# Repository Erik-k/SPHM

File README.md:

# SPHM
Solar Powered Home Monitor

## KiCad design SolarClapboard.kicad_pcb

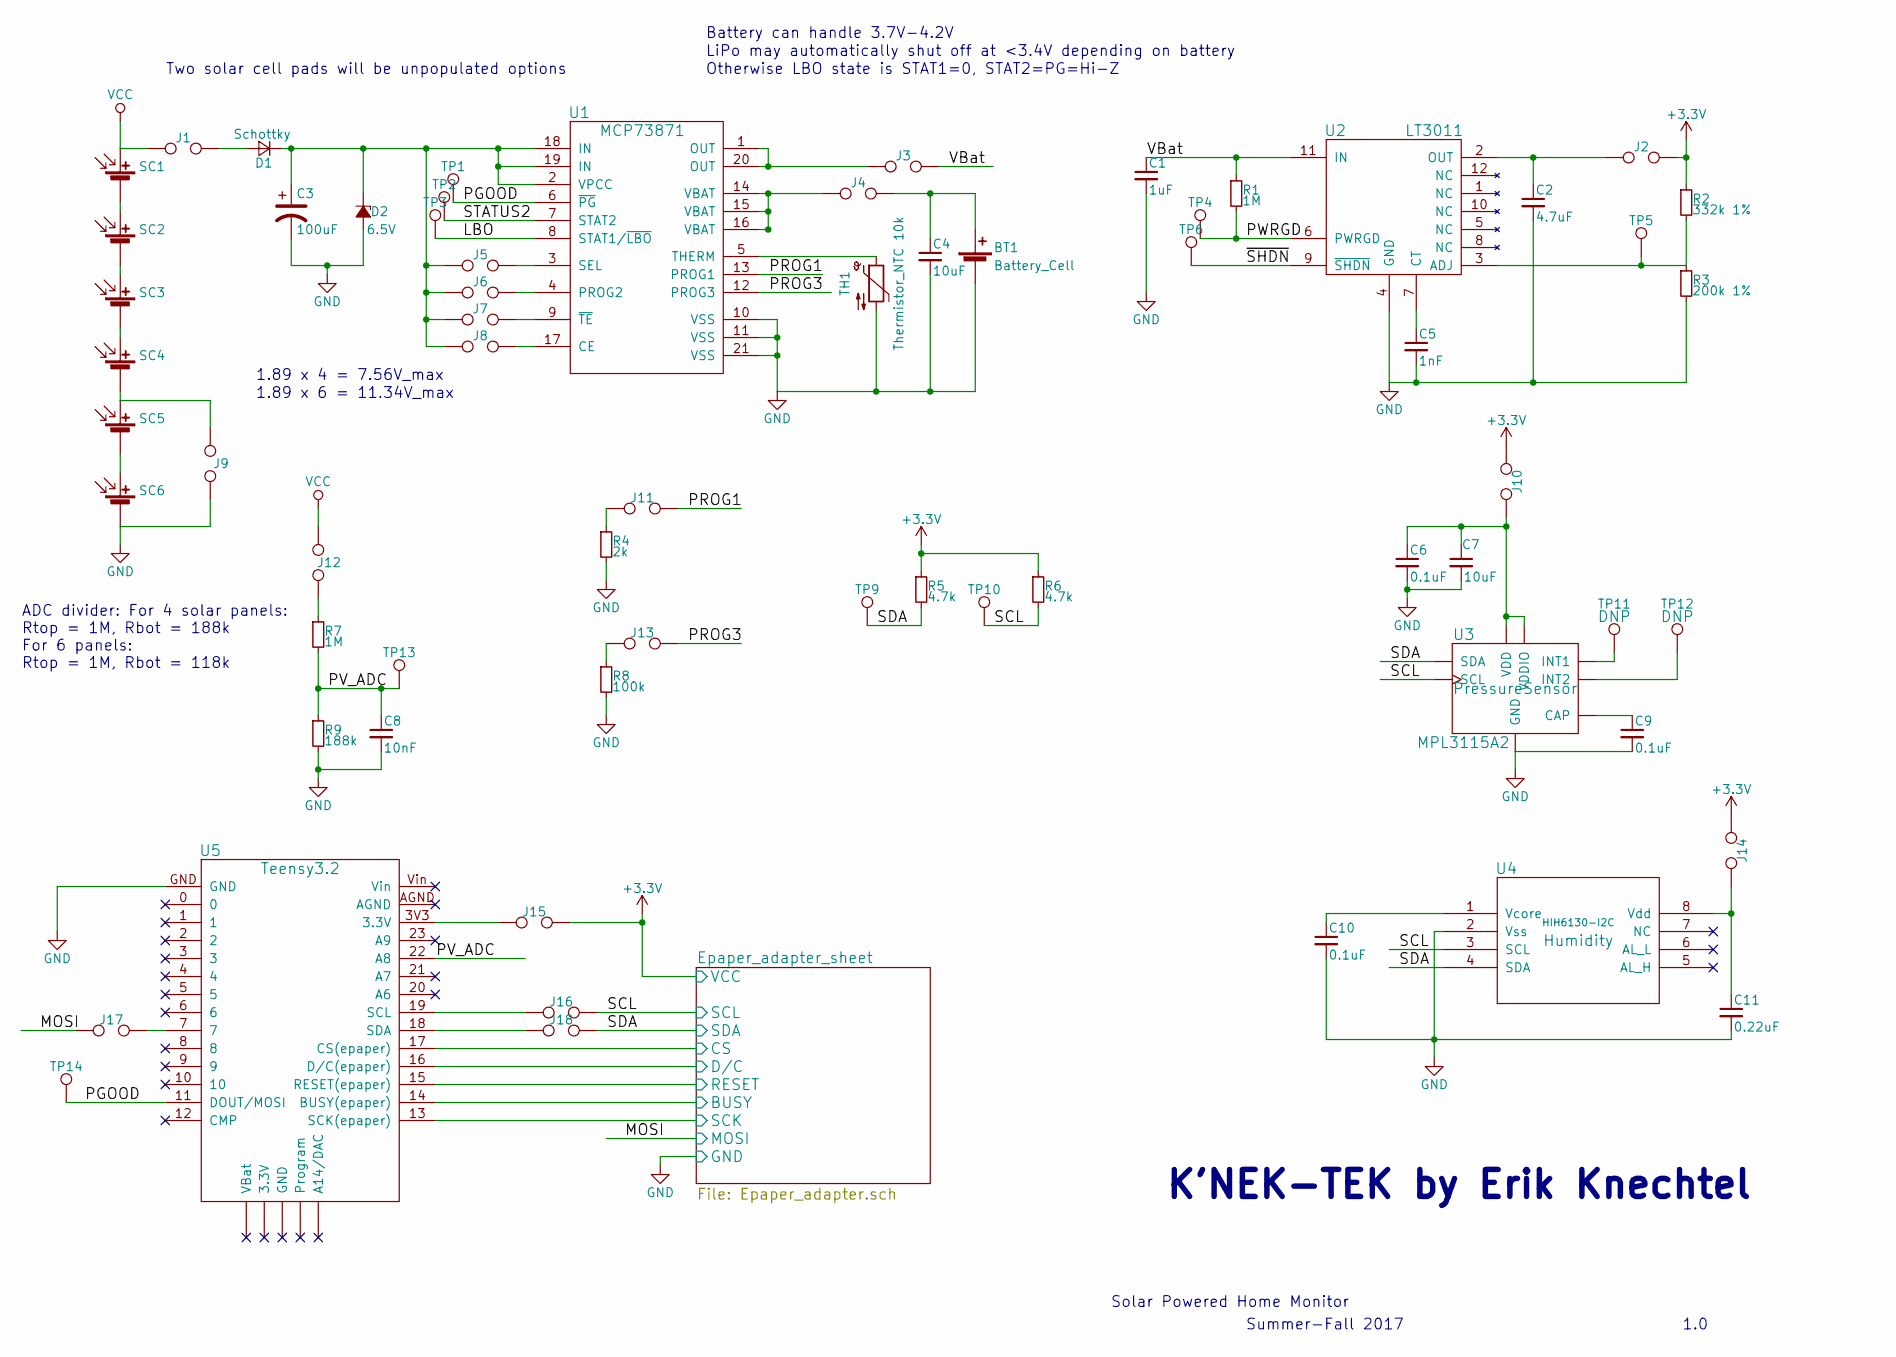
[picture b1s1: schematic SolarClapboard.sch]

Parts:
BT1: Battery_Cell; JST_PH_S2B-PH-SM4-TB_02x2.00mm_Angled
C1: 1uF; C_1206_HandSoldering
C2: 4.7uF; C_1206_HandSoldering
C3: 100uF; CP_Radial_D5.0mm_P2.00mm
C4, C7: 10uF; CP_Radial_D5.0mm_P2.00mm
C5: 1nF; C_1206_HandSoldering
C6, C9, C10: 0.1uF; C_1206_HandSoldering
C8: 10nF; C_1206_HandSoldering
C11: 0.22uF; C_1206_HandSoldering
D1: Schottky; D_SOD-323_HandSoldering; MFG_PN CUS08F30,H3F
D2: 6.5V; D_SOD-323_HandSoldering; MFG_PN DDZ6V8ASF-7
J1, J2, J3, J4, J5, J6, J7, J8, J9, J10, J11, J12, J13, J14, J15, J16, J17, J18: TEST_2P; Test_Point_2Pads
R1, R7: 1M; R_1206_HandSoldering
R2: 332k 1%; R_1206_HandSoldering
R3: 200k 1%; R_1206_HandSoldering
R4: 2k; R_1206_HandSoldering
R5, R6: 4.7k; R_1206_HandSoldering
R8: 100k; R_1206_HandSoldering
R9: 188k; R_1206_HandSoldering
SC1, SC2, SC3, SC4, SC5, SC6: Solar_Cell; MONO_SOLAR_CELL_22MMx7MM_KXOB22-04X3F; MFG_PN KXOB22-04X3F
TH1: Thermistor_NTC 10k; R_Axial_DIN0204_L3.6mm_D1.6mm_P2.54mm_Vertical
TP1, TP2, TP3, TP4, TP5, TP6, TP9, TP10, TP11, TP12, TP13, TP14: TEST_1P; TestPointHole
U1: MCP73871; QFN-20-1EP_4x4mm_Pitch0.5mm
U2: LT3011; MSOP-12_3x4mm_Pitch0.65mm
U3: MPL3115A2; LGA-8_3x5mm_Pitch1.25mm_handsolder
U4: HIH6130-I2C; SO-8_5.3x6.2mm_Pitch1.27mm
U5: Teensy3.2; Teensy_Header_Straight_2x14_Pitch2.54mm

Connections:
+3V3: J2.2, J10.1, J14.1, J15.2, R2.1, R5.1, R6.1; also elsewhere on the board
/Epaper_adapter_sheet/BUSY: U5.14 (BUSY(epaper)); also elsewhere on the board
/Epaper_adapter_sheet/CS: U5.17 (CS(epaper)); also elsewhere on the board
/Epaper_adapter_sheet/D/C: U5.16 (D/C(epaper)); also elsewhere on the board
/Epaper_adapter_sheet/RESET: U5.15 (RESET(epaper)); also elsewhere on the board
/Epaper_adapter_sheet/SCK: U5.13 (SCK(epaper)); also elsewhere on the board
/LBO: TP3.1, U1.8 (STAT1/~LBO)
/MOSI: J17.1; also elsewhere on the board
/PGOOD: TP1.1, TP14.1, U1.6 (~PG), U5.11 (DOUT/MOSI)
/PROG1: J11.2, U1.13 (PROG1)
/PROG3: J13.2, U1.12 (PROG3)
/PV_ADC: C8.1, R7.2, R9.1, TP13.1, U5.22 (A8)
/PWRGD: R1.2, TP4.1, U2.6 (PWRGD)
/SCL: J16.2, R6.2, TP10.1, U3.8 (SCL), U4.3 (SCL)
/SDA: J18.2, R5.2, TP9.1, U3.7 (SDA), U4.4 (SDA)
/STATUS2: TP2.1, U1.7 (STAT2)
/VBat: C1.1, J3.2, R1.1, U2.11 (IN)
/~SHDN: TP6.1, U2.9 (~SHDN)
unnamed: BT1.1 (+), C4.1, J4.2
unnamed: C2.1, J2.1, U2.2 (OUT)
unnamed: C3.1, D1.1 (K), D2.1 (K), J5.1, J6.1, J7.1, J8.1, U1.2 (VPCC), U1.18 (IN), U1.19 (IN)
unnamed: C5.1, U2.7 (CT)
unnamed: C6.1, C7.1, J10.2, U3.1 (VDD), U3.4 (VDDIO)
unnamed: C9.1, U3.2 (CAP)
unnamed: C10.1, U4.1 (Vcore)
unnamed: C11.1, J14.2, U4.8 (Vdd)
unnamed: D1.2 (A), J1.2
unnamed: J3.1, U1.1 (OUT), U1.20 (OUT)
unnamed: J4.1, U1.14 (VBAT), U1.15 (VBAT), U1.16 (VBAT)
unnamed: J5.2, U1.3 (SEL)
unnamed: J6.2, U1.4 (PROG2)
unnamed: J7.2, U1.9 (~TE)
unnamed: J8.2, U1.17 (CE)
unnamed: J9.1, SC4.2 (-), SC5.1 (+)
unnamed: J11.1, R4.1
unnamed: J12.2, R7.1
unnamed: J13.1, R8.1
unnamed: J15.1, U5.3V3 (3.3V)
unnamed: J16.1, U5.19 (SCL)
unnamed: J17.2, U5.7
unnamed: J18.1, U5.18 (SDA)
unnamed: R2.2, R3.1, TP5.1, U2.3 (ADJ)
unnamed: SC1.2 (-), SC2.1 (+)
unnamed: SC2.2 (-), SC3.1 (+)
unnamed: SC3.2 (-), SC4.1 (+)
unnamed: SC5.2 (-), SC6.1 (+)
unnamed: TH1.1, U1.5 (THERM)
unnamed 74: U5.2; also elsewhere on the board
unnamed 75: U5.3; also elsewhere on the board
unnamed: TP11.1, U3.6 (INT1)
unnamed: TP12.1, U3.5 (INT2)
unnamed 78: U5.4; also elsewhere on the board
unnamed 79: U5.21 (A7); also elsewhere on the board
unnamed 80: U5.20 (A6); also elsewhere on the board
unnamed 81: U5.0; also elsewhere on the board
unnamed 82: U5.1; also elsewhere on the board
unnamed 83: U5.23 (A9); also elsewhere on the board
unnamed 84: U5.5; also elsewhere on the board
unnamed 85: U5.6; also elsewhere on the board
unnamed 86: U5.8; also elsewhere on the board
unnamed 87: U5.9; also elsewhere on the board
unnamed 88: U5.10; also elsewhere on the board
unnamed 89: U5.12 (CMP); also elsewhere on the board
VCC: J1.1, J12.1, SC1.1 (+)

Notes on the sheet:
Solar Powered Home Monitor
Summer-Fall 2017
K'NEK-TEK by Erik Knechtel
1.0
Battery can handle 3.7V-4.2V
Two solar cell pads will be unpopulated options
LiPo may automatically shut off at <3.4V depending on battery
Otherwise LBO state is STAT1=0, STAT2=PG=Hi-Z
1.89 x 4 = 7.56V_max
1.89 x 6 = 11.34V_max
ADC divider: For 4 solar panels: Rtop = 1M, Rbot = 188k For 6 panels: Rtop = 1M, Rbot = 118k

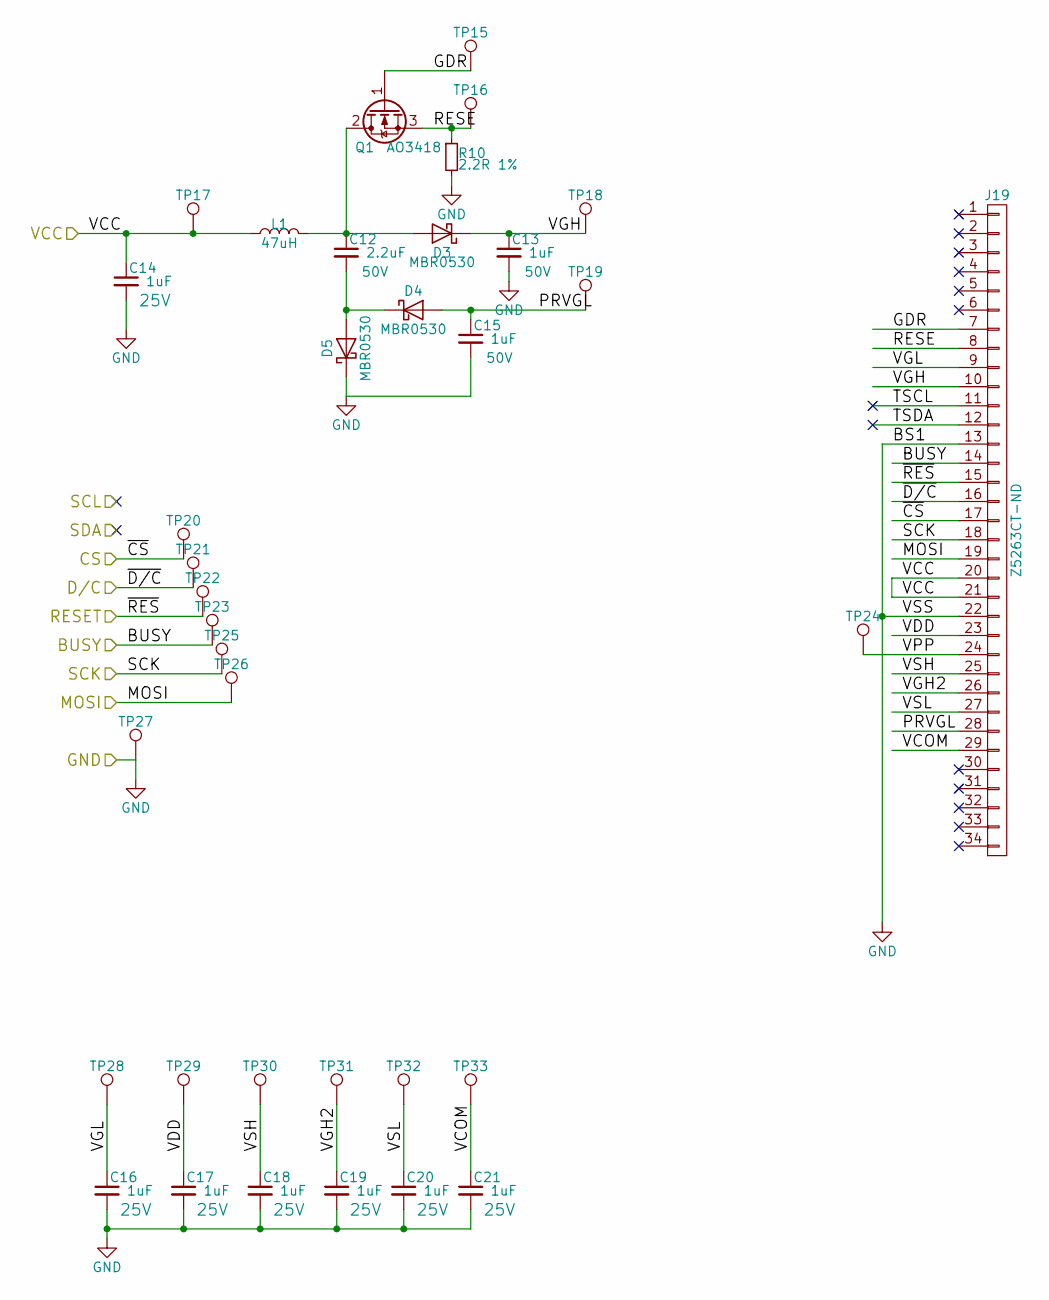
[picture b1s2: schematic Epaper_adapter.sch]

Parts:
C12: 2.2uF; C_1206_HandSoldering; Voltage 50V
C13, C15: 1uF; C_1206_HandSoldering; Voltage 50V
C14, C16, C17, C18, C19, C20, C21: 1uF; C_1206_HandSoldering; Voltage 25V
D3, D4, D5: MBR0530; D_SOD-123
J19: Z5263CT-ND; FPC_34
L1: 47uH; L_Coilcraft_XAL5030
Q1: AO3418; SOT-23
R10: 2.2R 1%; R_1206_HandSoldering
TP15, TP16, TP17, TP18, TP19, TP20, TP21, TP22, TP23, TP24, TP25, TP26, TP27, TP28, TP29, TP30, TP31, TP32, TP33: TEST_1P; TestPointHole

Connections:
+3V3: C14.1, J19.20, J19.21, L1.1, TP17.1; also elsewhere on the board
/Epaper_adapter_sheet/BUSY: J19.14, TP23.1; also elsewhere on the board
/Epaper_adapter_sheet/CS: J19.17, TP20.1; also elsewhere on the board
/Epaper_adapter_sheet/D/C: J19.16, TP21.1; also elsewhere on the board
/Epaper_adapter_sheet/GDR: J19.7, Q1.1 (G), TP15.1
/Epaper_adapter_sheet/PRVGL: C15.1, D4.2 (A), J19.28, TP19.1
/Epaper_adapter_sheet/RESE: J19.8, Q1.3 (S), R10.1, TP16.1
/Epaper_adapter_sheet/RESET: J19.15, TP22.1; also elsewhere on the board
/Epaper_adapter_sheet/SCK: J19.18, TP25.1; also elsewhere on the board
/Epaper_adapter_sheet/TSCL: J19.11
/Epaper_adapter_sheet/TSDA: J19.12
/Epaper_adapter_sheet/VCOM: C21.1, J19.29, TP33.1
/Epaper_adapter_sheet/VDD: C17.1, J19.23, TP29.1
/Epaper_adapter_sheet/VGH: C13.1, D3.1 (K), J19.10, TP18.1
/Epaper_adapter_sheet/VGH2: C19.1, J19.26, TP31.1
/Epaper_adapter_sheet/VGL: C16.1, J19.9, TP28.1
/Epaper_adapter_sheet/VPP: J19.24, TP24.1
/Epaper_adapter_sheet/VSH: C18.1, J19.25, TP30.1
/Epaper_adapter_sheet/VSL: C20.1, J19.27, TP32.1
/MOSI: J19.19, TP26.1; also elsewhere on the board
unnamed: C12.1, D3.2 (A), L1.2, Q1.2 (D)
unnamed: C12.2, D4.1 (K), D5.2 (A)

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
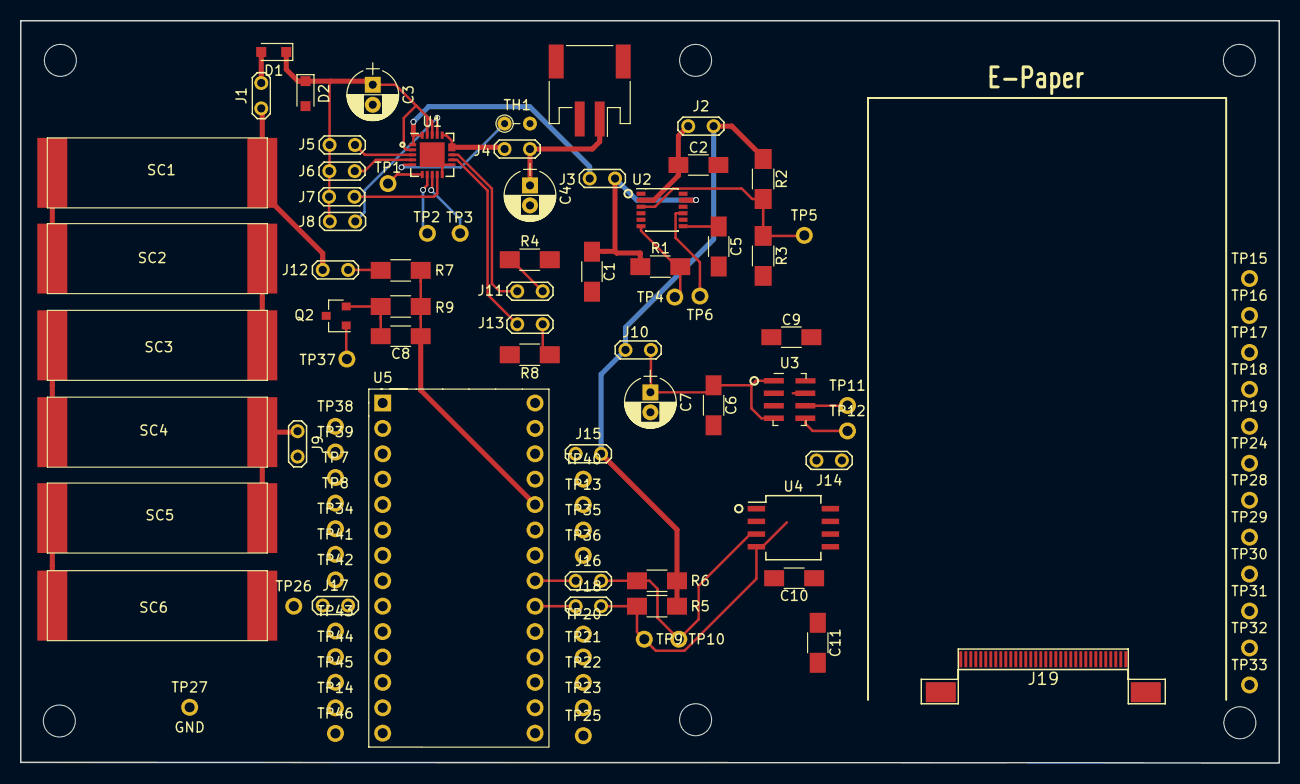
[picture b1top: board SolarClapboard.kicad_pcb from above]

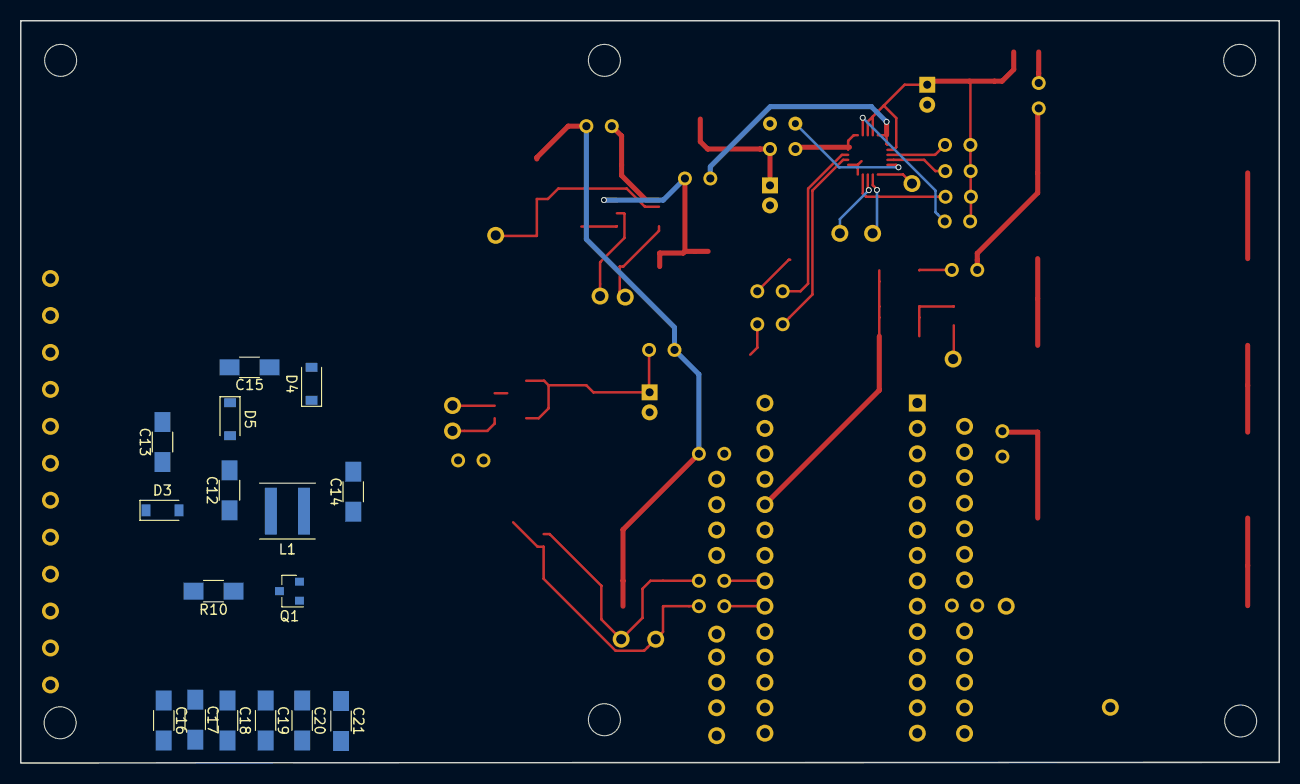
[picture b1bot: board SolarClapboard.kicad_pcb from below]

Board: 2 copper layers, 125.9 x 74.2 mm, 117 parts (16 on the bottom side), 80 nets.

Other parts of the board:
Q2: AO3418; SOT-23
TP7, TP8, TP34, TP35, TP36, TP37, TP38, TP39, TP40, TP41, TP42, TP43, TP44, TP45, TP46: TEST_1P; TestPointHole

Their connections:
unnamed: Q2.1, TP37.1
unnamed 74: TP7.1; also elsewhere on the board
unnamed 75: TP8.1; also elsewhere on the board
unnamed 78: TP34.1; also elsewhere on the board
unnamed 79: TP35.1; also elsewhere on the board
unnamed 80: TP36.1; also elsewhere on the board
unnamed 81: TP38.1; also elsewhere on the board
unnamed 82: TP39.1; also elsewhere on the board
unnamed 83: TP40.1; also elsewhere on the board
unnamed 84: TP41.1; also elsewhere on the board
unnamed 85: TP42.1; also elsewhere on the board
unnamed 86: TP43.1; also elsewhere on the board
unnamed 87: TP44.1; also elsewhere on the board
unnamed 88: TP45.1; also elsewhere on the board
unnamed 89: TP46.1; also elsewhere on the board

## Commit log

2017-10-17 First upload
    Uploading v1.0 as it stands. Schematic is nearly done, haven't gone to layout yet.
2017-10-19 Add files via upload
    Trying to figure out whether to hook up the PGOOD and PWRGOOD and SHDN and so on.
2017-10-30 Add files via upload
    Working on the BOM and footprints.
2017-11-02 Add files via upload
    Ready to do layout. All footprints correct, no board size chosen yet. Made outline for 6cm x 3.5cm e-paper.
2017-11-17 Add files via upload
    Ready for layout. Fixed test point hole size.
2017-11-27 Add files via upload
    Added the arduino code
2017-11-30 Add files via upload
    Layout in progress. Board is <5" x <3"
